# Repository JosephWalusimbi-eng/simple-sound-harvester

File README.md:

# simpler sound harvester

A capstone-friendly, simplified piezoelectric energy harvester: a 5-part
passive design (piezo input -> bridge rectifier -> storage cap -> Zener
clamp -> output terminal), down from ~40 components in the original design.

- [`about.txt`](about.txt) - design rationale and simplifications
- [`kicad/`](kicad/) - KiCad schematic, PCB layout, and BOM

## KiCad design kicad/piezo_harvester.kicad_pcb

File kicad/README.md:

# Piezo Energy Harvester -- Simplified 5-Part Passive Design

A KiCad project implementing the simplified schematic described in
[`../about.txt`](../about.txt):

```
Piezo Header -> Bridge Rectifier -> Storage Cap -> Zener Diode Clamp -> Output Terminal
```

## Files

- `piezo_harvester.kicad_pro` - KiCad project file
- `piezo_harvester.kicad_sch` - Schematic (flat, single sheet)
- `piezo_harvester.kicad_pcb` - 2-layer, through-hole PCB layout
- `BOM.csv` - Bill of materials

## Circuit

| Ref | Part | Role |
|-----|------|------|
| J1 | 2-pin screw terminal | Piezo element input |
| U1 | Bridge rectifier (or 4x 1N5817 diodes) | Full-wave rectification of the piezo AC output |
| C1 | 100 uF electrolytic capacitor | Smoothing / energy storage |
| D1 | 5.1 V Zener diode | Clamps `VOUT_PLUS` to a safe voltage |
| J2 | 2-pin screw terminal | Output to a supercapacitor/battery and/or load |

Nets: `PIEZO_A`, `PIEZO_B` (bridge inputs), `VOUT_PLUS` and `GND` (rectified/clamped
output rail, shared by C1, D1 and J2).

All parts are through-hole, and the PCB uses only basic rectangular/circular
pads and hand-routable orthogonal traces on `F.Cu`, per the "5 or 6 component,
hand-routable 2-layer board" goal in `about.txt`.

## How this was built / how to verify it

KiCad is not installed in the environment this was built in, so these files
were generated programmatically (coordinates computed in Python, not typed by
hand) and checked two ways instead of visually:

1. Parsed back with the `kiutils` library to confirm the S-expression syntax
   is well-formed.
2. A connectivity check (`check_connectivity` logic) confirms every pad that
   should share a net in the circuit (e.g. U1 pin 3, C1 pin 1, D1 pin 2, J2
   pin 1 all on `VOUT_PLUS`) actually does, and nothing unintended is merged.

**Before relying on this for a build, open it in KiCad (8.x recommended) and:**
- Run Schematic ERC and PCB DRC (Inspect menu).
- Visually check silkscreen/footprint placement and courtyards don't overlap.
- Confirm footprint choices match the exact parts you buy (pad sizes/pitches
  here are reasonable defaults, not pulled from a manufacturer datasheet).

## Design notes / what was simplified

See `../about.txt` for the full rationale. In short: one piezo input instead
of three, a single packaged bridge rectifier (or 4 diodes) instead of 12
SMD diodes, a passive cap+Zener clamp instead of the BQ25570 MPPT charger,
and a bare screw-terminal output instead of a USB boost stage -- dropping the
part count from ~40 to 5.

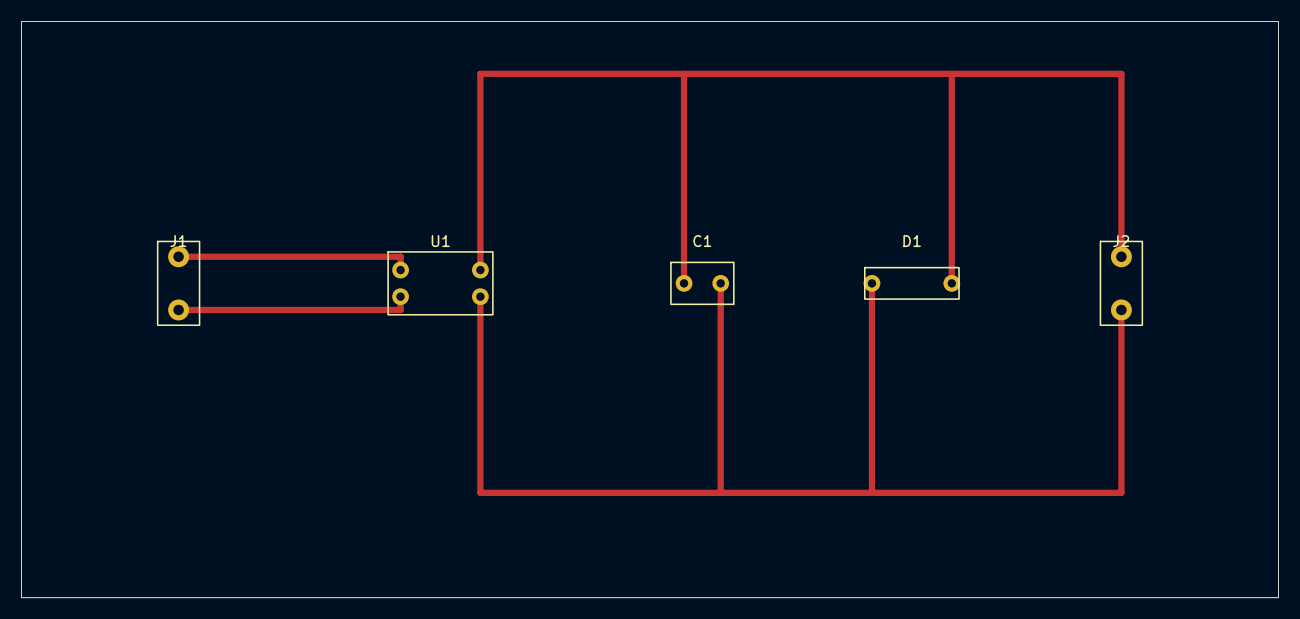
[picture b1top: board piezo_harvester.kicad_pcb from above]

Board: 2 copper layers, 120.0 x 55.0 mm, 5 parts (0 on the bottom side), 4 nets.

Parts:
C1: 100uF_16V; C_Polarized
D1: 1N5231B_5V1; D_Zener
J1: Piezo_Input; Screw_Terminal_2
J2: To_Storage_Load; Screw_Terminal_2
U1: HD01_MB10S; Bridge_Rectifier

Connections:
GND: C1.2, D1.1, J2.2, U1.4
PIEZO_A: J1.1, U1.1
PIEZO_B: J1.2, U1.2
VOUT_PLUS: C1.1, D1.2, J2.1, U1.3
